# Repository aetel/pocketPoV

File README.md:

# pocketPoV
This little device can serve as a Persistence of View (PoV) display. Just make it swing in the air and it will display a message.

To program the ATtiny85 you may follow this guide:
http://highlowtech.org/?p=1706

---

pocketPoV and its surrounding materials are published under [CC BY-SA 4.0](https://creativecommons.org/licenses/by-sa/4.0/)

pocketPoV was designed by [RS](https://github.com/rsre "RS") & CBS for Telecom Electronics Association [AETEL](http://aetel.io), based at the Campus Sur of [Universidad Politécnica de Madrid](http://upm.es).

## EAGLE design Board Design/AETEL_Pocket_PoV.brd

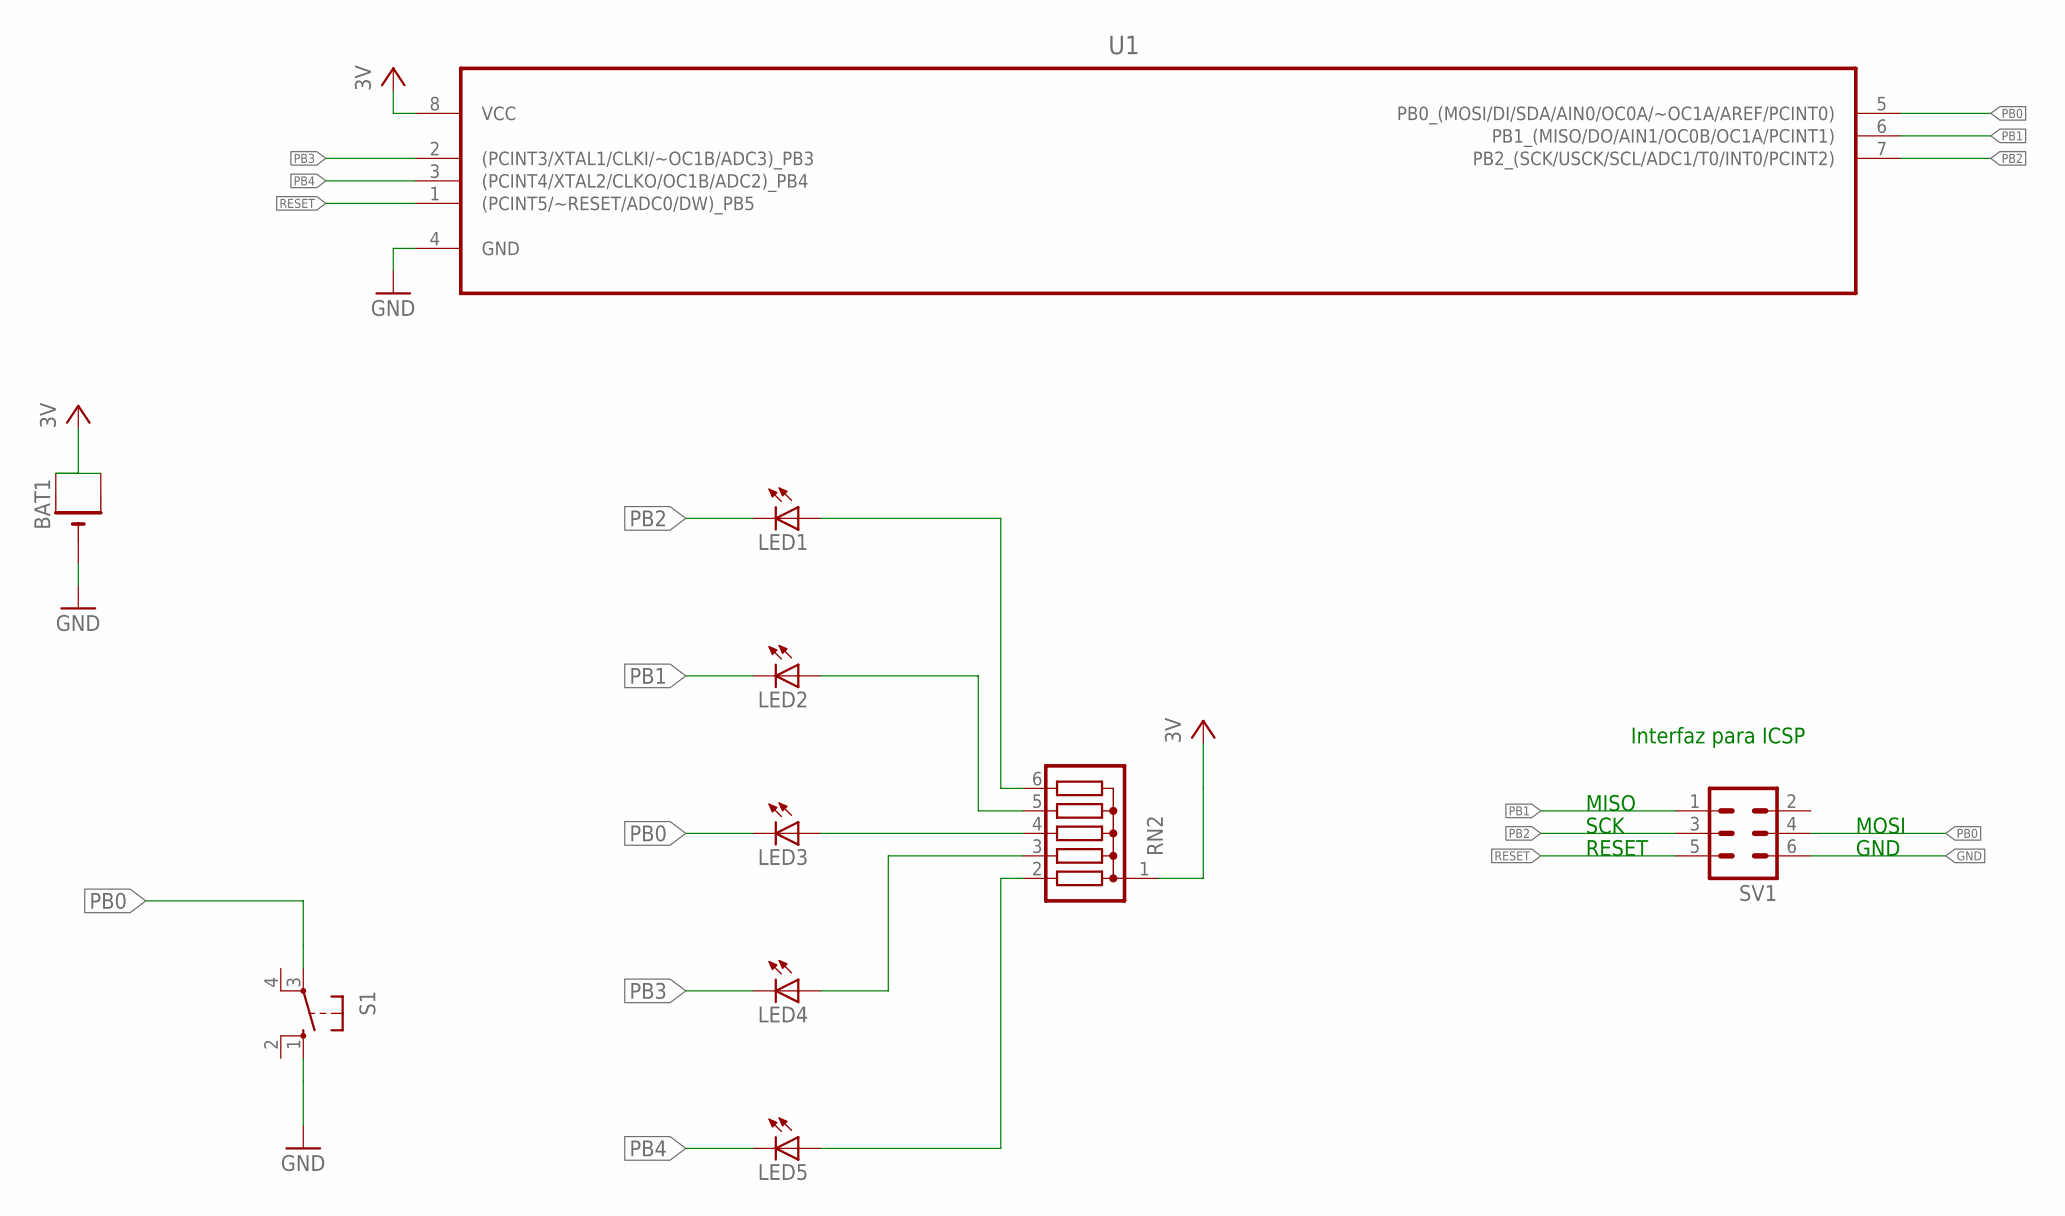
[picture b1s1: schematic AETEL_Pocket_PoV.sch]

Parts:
BAT1: CR2032THM; CR2032-THRU
LED1, LED2, LED3, LED4, LED5: LEDSQUARE_LED5MM; SQUARE_LED5MM
RN2: G05R; SIL6
S1: 10-XX; B3F-10XX
SV1: MA03-2
U1: ATTINY85-20PU; DIP254P762X533-8

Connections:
GND: BAT1.-, S1.1 (S), SV1.6, U1.4 (GND)
unnamed: LED3.A, RN2.4
unnamed: LED1.A, RN2.6
unnamed: LED2.A, RN2.5
unnamed: LED5.A, RN2.2
unnamed: LED4.A, RN2.3
PB0: LED3.K (C), S1.3, SV1.4, U1.5 (PB0_(MOSI/DI/SDA/AIN0/OC0A/~OC1A/AREF/P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)
PB1: LED2.K (C), SV1.1, U1.6 (PB1_(MISO/DO/AIN1/OC0B/OC1A/PCINT1))
PB2: LED1.K (C), SV1.3, U1.7 (PB2_(SCK/USCK/SCL/ADC1/T0/INT0/PCINT2))
PB3: LED4.K (C), U1.2 ((PCINT3/XTAL1/CLKI/~OC1B/ADC3)_PB3)
PB4: LED5.K (C), U1.3 ((PCINT4/XTAL2/CLKO/OC1B/ADC2)_PB4)
RESET: SV1.5, U1.1 ((PCINT5/~RESET/ADC0/DW)_PB5)
VCC: BAT1.+1 (+), BAT1.+2 (+1), RN2.1, U1.8 (VCC)

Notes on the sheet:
MOSI
MISO
SCK
RESET
GND
Interfaz para ICSP

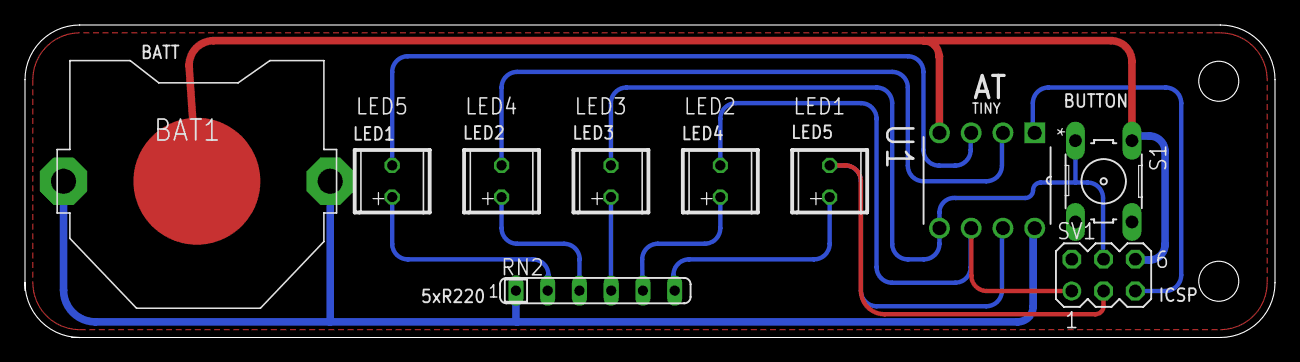
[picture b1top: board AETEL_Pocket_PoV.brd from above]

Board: 2 copper layers, 100.0 x 25.0 mm, 10 parts (0 on the bottom side), 13 nets.

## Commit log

2016-04-28 Added BoM, images and code
    Added BoM.
    Added board image.
    Added RS&CBS colab logo.
    Added first version of code.
2017-03-08 Added board design, working picture and license
2017-03-08 Made image smaller and fixed link

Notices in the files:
README.md:
CC0
